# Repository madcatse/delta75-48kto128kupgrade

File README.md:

# 128k RAM expansion for ZX48k
Upgrade ZX Spectrum 48k with 128k of RAM and play all the games that you couldn't play before. The sound will stay as before, but you can buy an extension module (based on AY-3-8912 or AY-3-8910) to make it sound as ZX Spectrum 128k.

In order to make the RAM expansion work, a small modification to your ZX Spectrum 48k is required to disable 32k upper RAM.

For Issue 2-3-4, on IC23 cut and bend pin 1 and connect it to pin 14 (+5V). For Issue 5-6 cut pin 34 (CASL) on ZX8401 and connect it's via (not the pin) to pin 40 (+5V).

Попробовать восьмой пин U39 поднять и посадить туда +5В

https://spectrumcomputing.co.uk/forums/viewtopic.php?t=2616

With this mod without the RAM expansion, your ZX Spectrum 48k will work as ZX Spectrum 16k. 

Original page: https://velesoft.speccy.cz/zx/external_128kb_upgrade/index.htm

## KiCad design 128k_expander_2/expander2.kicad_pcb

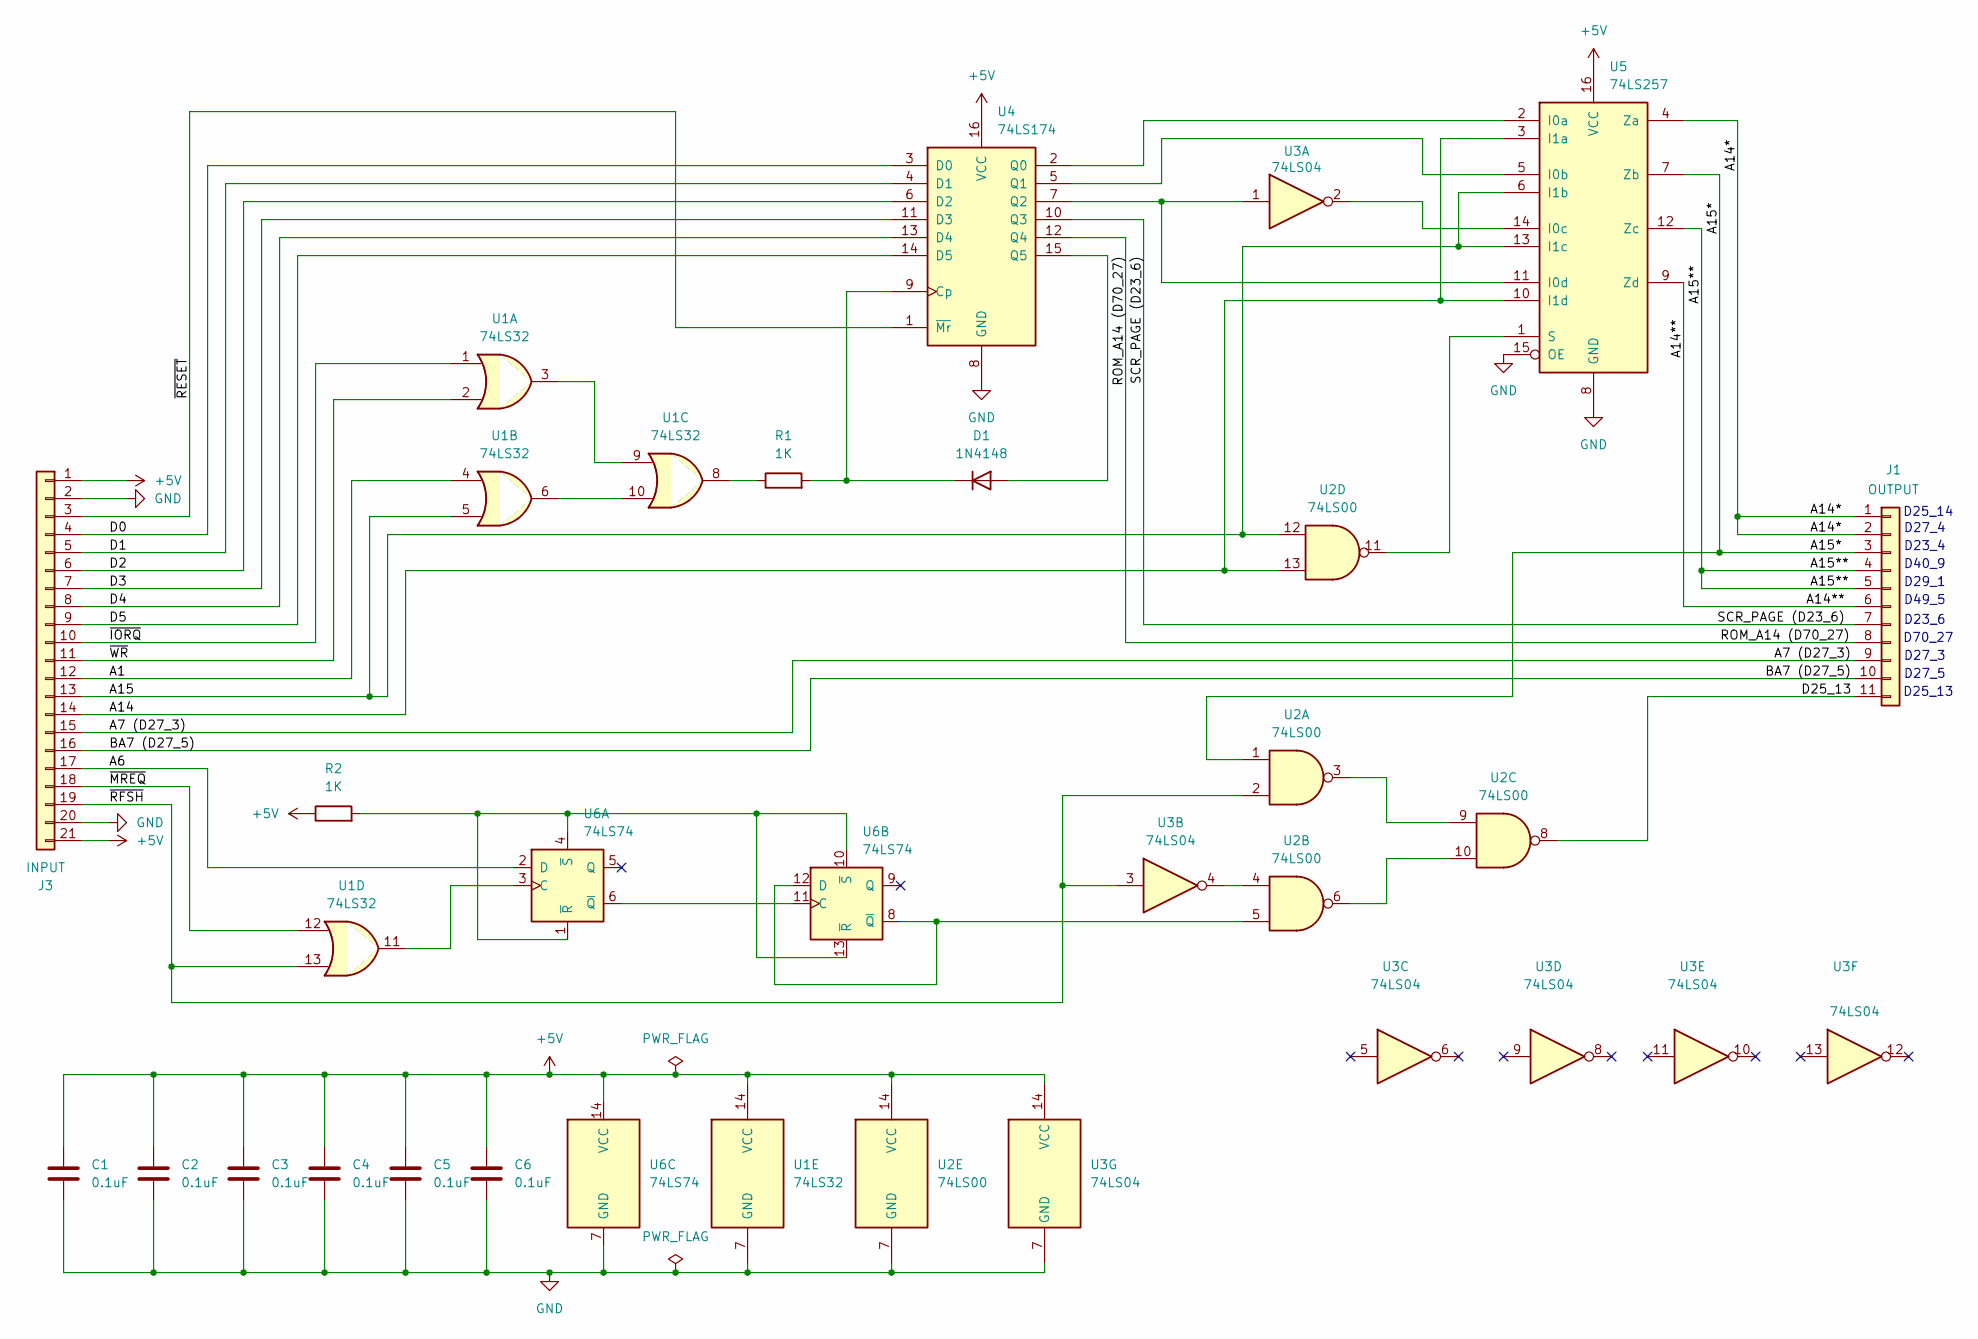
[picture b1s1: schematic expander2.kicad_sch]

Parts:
C1, C2, C3, C4, C5, C6: 0.1uF; C_Disc_D7.5mm_W2.5mm_P5.00mm
D1: 1N4148; D_DO-35_SOD27_P10.16mm_Horizontal
J1: OUTPUT; PinHeader_1x11_P2.54mm_Vertical
J3: INPUT; PinHeader_1x21_P2.54mm_Vertical
R1, R2: 1K; R_Axial_DIN0207_L6.3mm_D2.5mm_P10.16mm_Horizontal
U1: 74LS32; DIP-14_W7.62mm_Socket_LongPads
U2: 74LS00; DIP-14_W7.62mm_Socket_LongPads
U3: 74LS04; DIP-14_W7.62mm_Socket_LongPads
U4: 74LS174; DIP-16_W7.62mm_Socket_LongPads
U5: 74LS257; DIP-16_W7.62mm_Socket_LongPads
U6: 74LS74; DIP-14_W7.62mm_Socket_LongPads

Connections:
+5V: C1.1, C2.1, C3.1, C4.1, C5.1, C6.1, J3.1, J3.21, R2.1, U1.14 (VCC), U2.14 (VCC), U3.14 (VCC), U4.16 (VCC), U5.16 (VCC), U6.14 (VCC)
/A1: J3.12, U1.4
/A6: J3.17, U6.2 (D)
/A7 (D27_3): J1.9, J3.15
/A14: J3.14, U2.13, U5.3 (I1a), U5.10 (I1d)
/A14*: J1.1, J1.2, U5.4 (Za)
/A14**: J1.6, U5.9 (Zd)
/A15: J3.13, U1.5, U2.12, U5.6 (I1b), U5.13 (I1c)
/A15*: J1.3, U2.1, U5.7 (Zb)
/A15**: J1.4, J1.5, U5.12 (Zc)
/BA7 (D27_5): J1.10, J3.16
/D0: J3.4, U4.3 (D0)
/D1: J3.5, U4.4 (D1)
/D2: J3.6, U4.6 (D2)
/D3: J3.7, U4.11 (D3)
/D4: J3.8, U4.13 (D4)
/D5: J3.9, U4.14 (D5)
/D25_13: J1.11, U2.8
/ROM_A14 (D70_27): J1.8, U4.12 (Q4)
/SCR_PAGE (D23_6): J1.7, U4.10 (Q3)
/~IORQ: J3.10, U1.1
/~MREQ: J3.18, U1.12
/~RESET: J3.3, U4.1 (~Mr)
/~RFSH: J3.19, U1.13, U2.2, U3.3
/~WR: J3.11, U1.2
GND: C1.2, C2.2, C3.2, C4.2, C5.2, C6.2, J3.2, J3.20, U1.7 (GND), U2.7 (GND), U3.7 (GND), U4.8 (GND), U5.8 (GND), U5.15 (OE), U6.7 (GND)
unnamed: D1.2 (A), U4.15 (Q5)
unnamed: D1.1 (K), R1.2, U4.9 (Cp)
unnamed: R1.1, U1.8
unnamed: U1.3, U1.9
unnamed: U1.6, U1.10
unnamed: U2.3, U2.9
unnamed: U2.4, U3.4
unnamed: U2.6, U2.10
unnamed: U4.2 (Q0), U5.2 (I0a)
unnamed: U4.5 (Q1), U5.5 (I0b)
unnamed: U3.1, U4.7 (Q2), U5.11 (I0d)
unnamed: U3.2, U5.14 (I0c)
unnamed: U2.11, U5.1 (S)
unnamed: U1.11, U6.3 (C)
unnamed: U6.6 (~Q), U6.11 (C)
unnamed: R2.2, U6.1 (~R), U6.4 (~S), U6.10 (~S), U6.13 (~R)
unnamed: U2.5, U6.8 (~Q), U6.12 (D)

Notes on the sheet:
D70_27
D25_14
D40_9
D27_3
D29_1
D27_4
D49_5
D23_4
D25_13
D23_6
D27_5

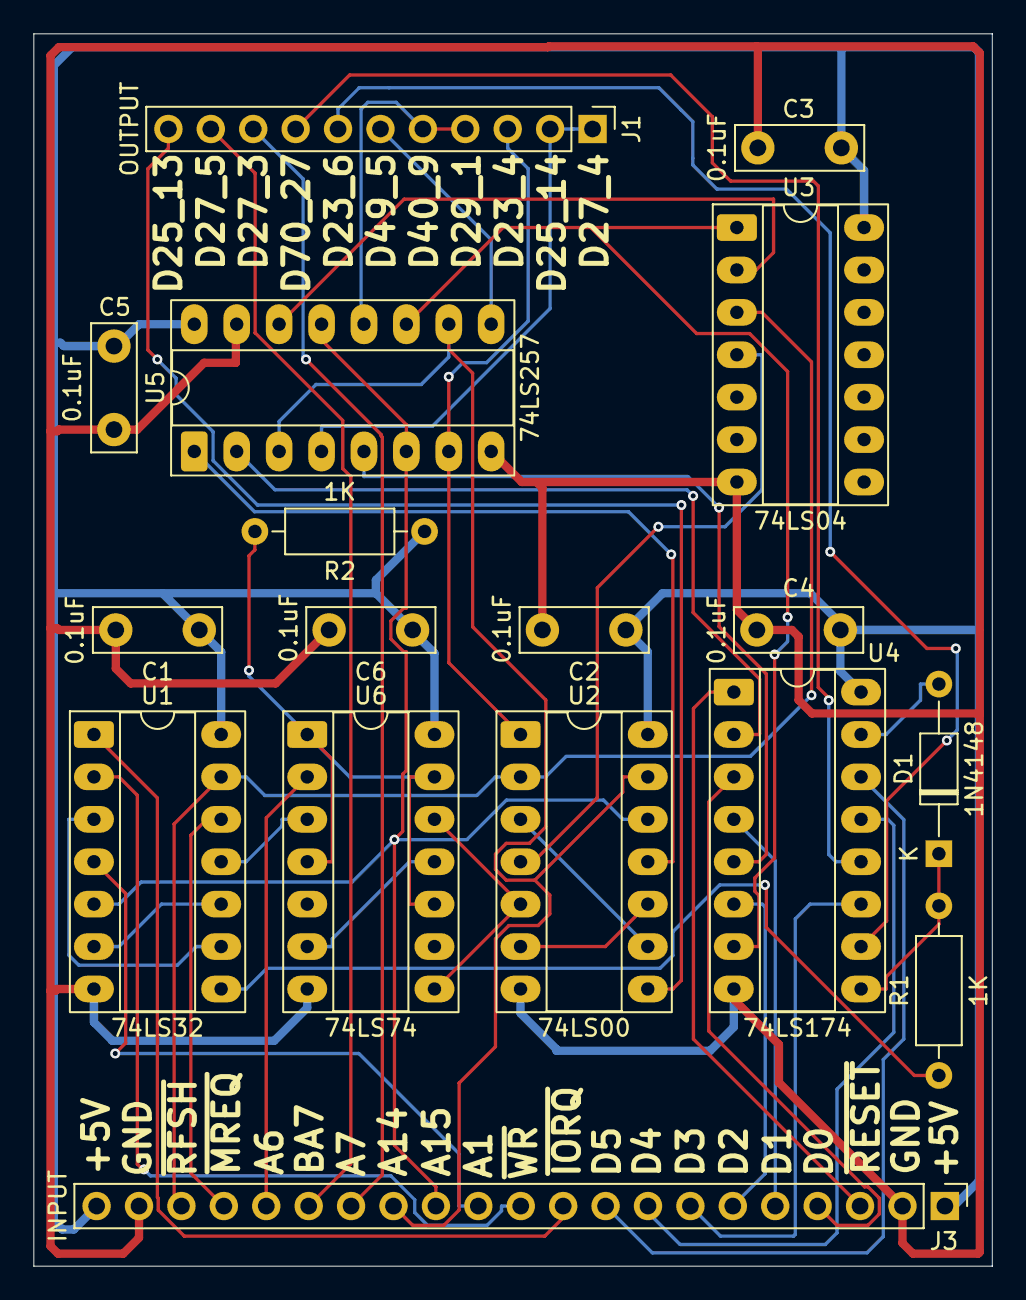
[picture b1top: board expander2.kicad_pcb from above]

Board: 2 copper layers, 57.4 x 73.8 mm, 17 parts (0 on the bottom side), 43 nets.

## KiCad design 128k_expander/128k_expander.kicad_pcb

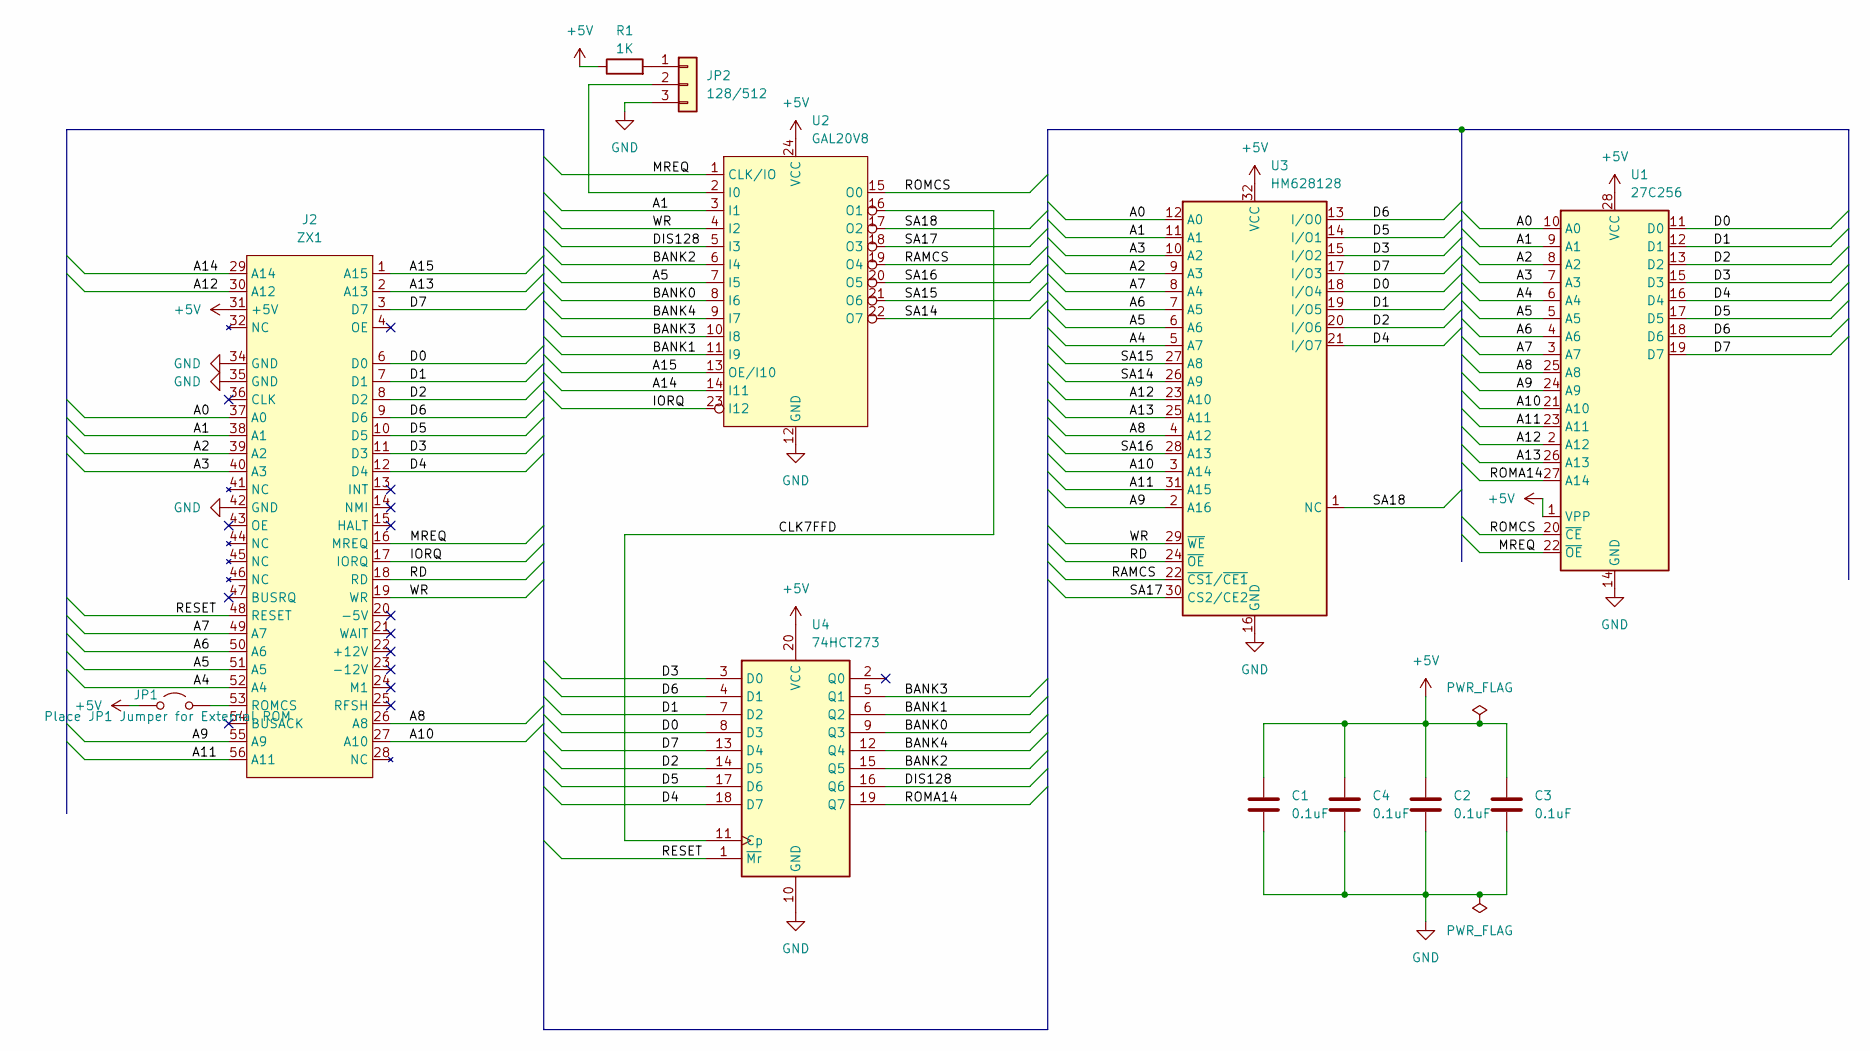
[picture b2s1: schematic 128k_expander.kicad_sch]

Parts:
C1, C2, C3, C4: 0.1uF; C_Disc_D7.5mm_W2.5mm_P5.00mm
J2: ZX1; ZX SPECTRUM EDGE CONNECTOR (HORIZONTAL)
JP1: Place JP1 Jumper for External ROM; PinHeader_1x02_P2.54mm_Vertical
JP2: 128/512; PinHeader_1x03_P2.54mm_Vertical
R1: 1K; R_Axial_DIN0207_L6.3mm_D2.5mm_P10.16mm_Horizontal
U1: 27C256; DIP-28_W15.24mm_LongPads
U2: GAL20V8; DIP-24_W7.62mm_LongPads
U3: HM628128; DIP-32_W15.24mm_LongPads
U4: 74HCT273; DIP-20_W7.62mm_LongPads

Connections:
+5V: C1.1, C2.1, C3.1, C4.1, J2.31 (+5V), JP1.1 (A), R1.1, U1.1 (VPP), U1.28 (VCC), U2.24 (VCC), U3.32 (VCC), U4.20 (VCC)
/A0: J2.37 (A0), U1.10 (A0), U3.12 (A0)
/A1: J2.38 (A1), U1.9 (A1), U2.3 (I1), U3.11 (A1)
/A2: J2.39 (A2), U1.8 (A2), U3.9 (A3)
/A3: J2.40 (A3), U1.7 (A3), U3.10 (A2)
/A4: J2.52 (A4), U1.6 (A4), U3.5 (A7)
/A5: J2.51 (A5), U1.5 (A5), U2.7 (I5), U3.6 (A6)
/A6: J2.50 (A6), U1.4 (A6), U3.7 (A5)
/A7: J2.49 (A7), U1.3 (A7), U3.8 (A4)
/A8: J2.26 (A8), U1.25 (A8), U3.4 (A12)
/A9: J2.55 (A9), U1.24 (A9), U3.2 (A16)
/A10: J2.27 (A10), U1.21 (A10), U3.3 (A14)
/A11: J2.56 (A11), U1.23 (A11), U3.31 (A15)
/A12: J2.30 (A12), U1.2 (A12), U3.23 (A10)
/A13: J2.2 (A13), U1.26 (A13), U3.25 (A11)
/A14: J2.29 (A14), U2.14 (I11)
/A15: J2.1 (A15), U2.13 (OE/I10)
/BANK0: U2.8 (I6), U4.9 (Q3)
/BANK1: U2.11 (I9), U4.6 (Q2)
/BANK2: U2.6 (I4), U4.15 (Q5)
/BANK3: U2.10 (I8), U4.5 (Q1)
/BANK4: U2.9 (I7), U4.12 (Q4)
/CLK7FFD: U2.16 (O1), U4.11 (Cp)
/D0: J2.6 (D0), U1.11 (D0), U3.18 (I/O4), U4.8 (D3)
/D1: J2.7 (D1), U1.12 (D1), U3.19 (I/O5), U4.7 (D2)
/D2: J2.8 (D2), U1.13 (D2), U3.20 (I/O6), U4.14 (D5)
/D3: J2.11 (D3), U1.15 (D3), U3.15 (I/O2), U4.3 (D0)
/D4: J2.12 (D4), U1.16 (D4), U3.21 (I/O7), U4.18 (D7)
/D5: J2.10 (D5), U1.17 (D5), U3.14 (I/O1), U4.17 (D6)
/D6: J2.9 (D6), U1.18 (D6), U3.13 (I/O0), U4.4 (D1)
/D7: J2.3 (D7), U1.19 (D7), U3.17 (I/O3), U4.13 (D4)
/DIS128: U2.5 (I3), U4.16 (Q6)
/IORQ: J2.17 (IORQ), U2.23 (I12)
/MREQ: J2.16 (MREQ), U1.22 (~OE), U2.1 (CLK/IO)
/RAMCS: U2.19 (O4), U3.22 (~CS1/~CE1)
/RD: J2.18 (RD), U3.24 (~OE)
/RESET: J2.48 (RESET), U4.1 (~Mr)
/ROMA14: U1.27 (A14), U4.19 (Q7)
/ROMCS: U1.20 (~CE), U2.15 (O0)
/SA14: U2.22 (O7), U3.26 (A9)
/SA15: U2.21 (O6), U3.27 (A8)
/SA16: U2.20 (O5), U3.28 (A13)
/SA17: U2.18 (O3), U3.30 (CS2/CE2)
/SA18: U2.17 (O2), U3.1 (NC)
/WR: J2.19 (WR), U2.4 (I2), U3.29 (~WE)
GND: C1.2, C2.2, C3.2, C4.2, J2.34 (GND), J2.35 (GND), J2.42 (GND), JP2.3, U1.14 (GND), U2.12 (GND), U3.16 (GND), U4.10 (GND)
unnamed: J2.53 (ROMCS), JP1.2 (B)
unnamed: JP2.1, R1.2
unnamed: JP2.2, U2.2 (I0)

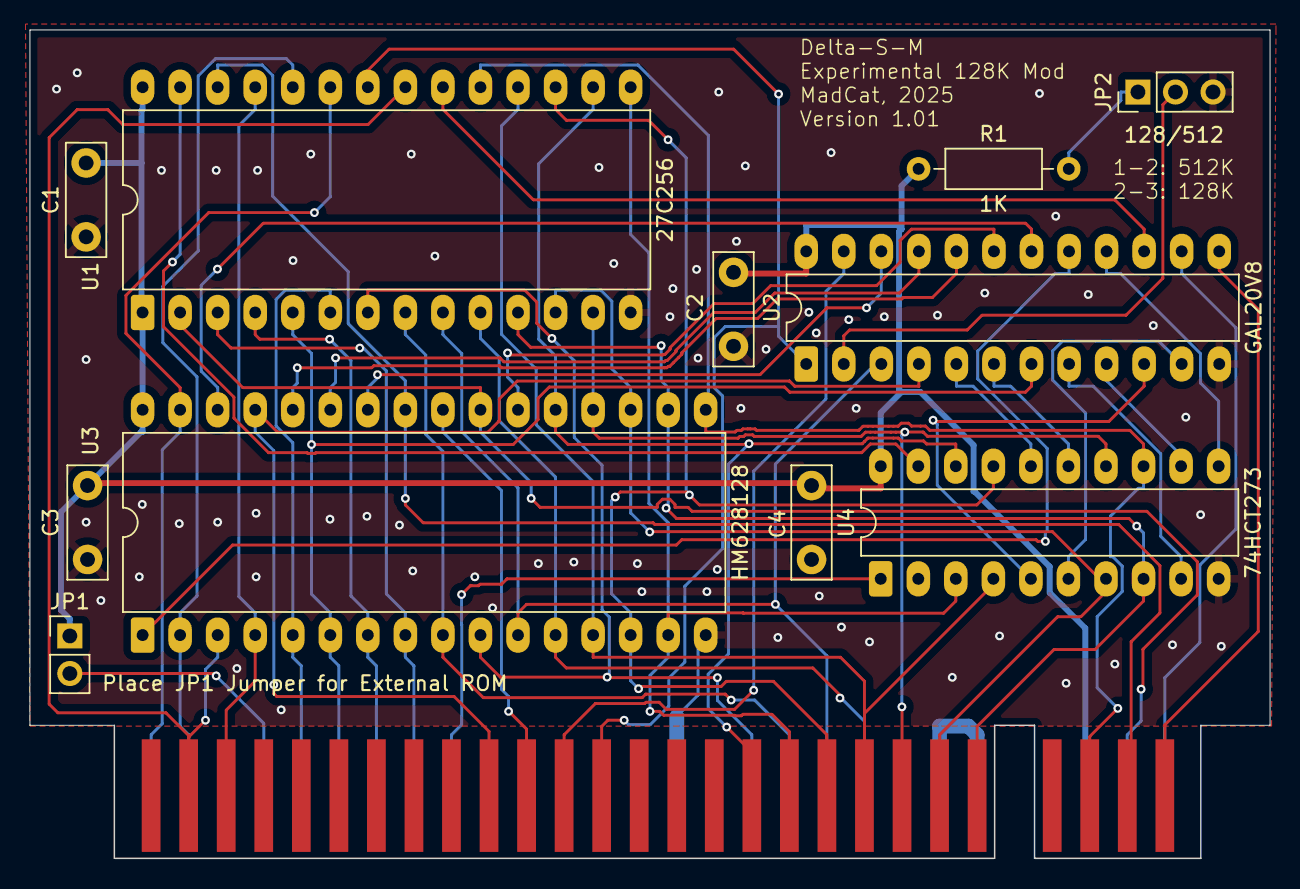
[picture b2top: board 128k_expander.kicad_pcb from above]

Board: 2 copper layers, 83.9 x 56.0 mm, 12 parts (0 on the bottom side), 49 nets.

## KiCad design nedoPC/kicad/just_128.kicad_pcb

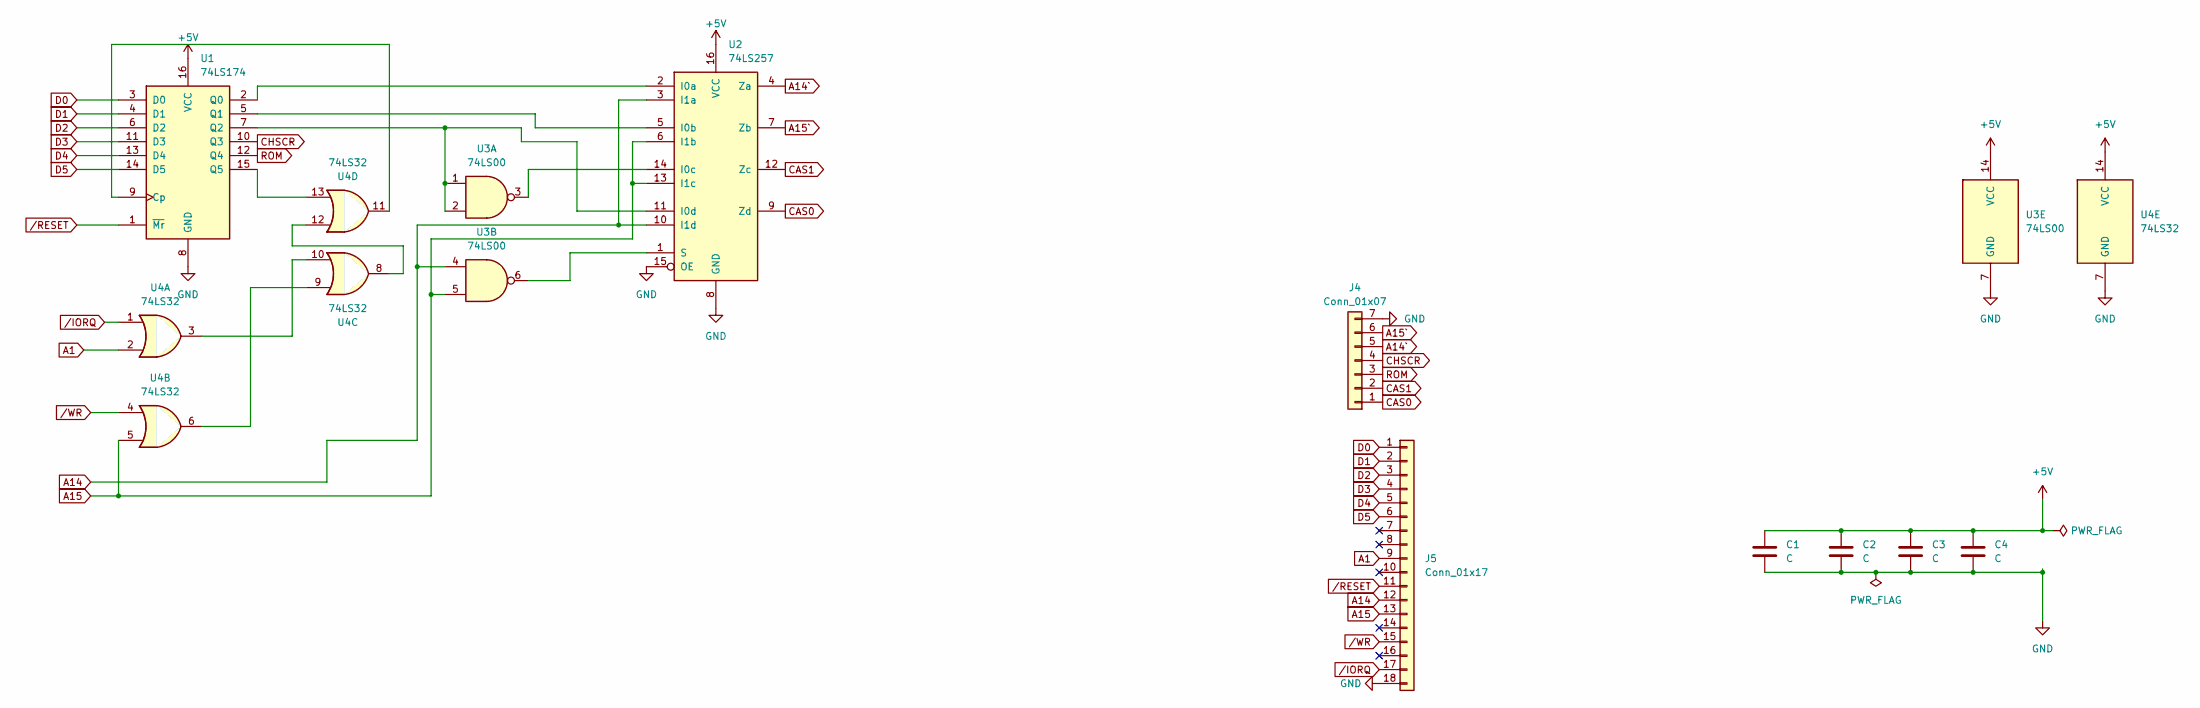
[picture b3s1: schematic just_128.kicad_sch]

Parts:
C1, C2, C3, C4: C; C_Disc_D7.0mm_W2.5mm_P5.00mm
J4: Conn_01x07; PinSocket_1x07_P2.54mm_Horizontal
J5: Conn_01x17; PinSocket_1x18_P2.54mm_Horizontal
U1: 74LS174; DIP-16_W7.62mm_Socket
U2: 74LS257; DIP-16_W7.62mm_Socket
U3: 74LS00; DIP-14_W7.62mm_Socket
U4: 74LS32; DIP-14_W7.62mm_Socket

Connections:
+5V: C1.1, C2.1, C3.1, C4.1, U1.16 (VCC), U2.16 (VCC), U3.14 (VCC), U4.14 (VCC)
A1: J5.9, U4.2
A14: J5.12, U2.3 (I1a), U2.10 (I1d), U3.4
A14`: J4.5, U2.4 (Za)
A15: J5.13, U2.6 (I1b), U2.13 (I1c), U3.5, U4.5
A15`: J4.6, U2.7 (Zb)
CAS0: J4.1, U2.9 (Zd)
CAS1: J4.2, U2.12 (Zc)
CHSCR: J4.4, U1.10 (Q3)
D0: J5.1, U1.3 (D0)
D1: J5.2, U1.4 (D1)
D2: J5.3, U1.6 (D2)
D3: J5.4, U1.11 (D3)
D4: J5.5, U1.13 (D4)
D5: J5.6, U1.14 (D5)
GND: C1.2, C2.2, C3.2, C4.2, J4.7, J5.18, U1.8 (GND), U2.8 (GND), U2.15 (OE), U3.7 (GND), U4.7 (GND)
unnamed: U1.9 (Cp), U4.11
unnamed: U1.2 (Q0), U2.2 (I0a)
unnamed: U1.5 (Q1), U2.5 (I0b)
unnamed: U1.7 (Q2), U2.11 (I0d), U3.1, U3.2
unnamed: U1.15 (Q5), U4.13
unnamed: U2.14 (I0c), U3.3
unnamed: U2.1 (S), U3.6
unnamed: U4.6, U4.9
unnamed: U4.3, U4.10
unnamed: U4.8, U4.12
ROM: J4.3, U1.12 (Q4)
/IORQ: J5.17, U4.1
/RESET: J5.11, U1.1 (~Mr)
/WR: J5.15, U4.4

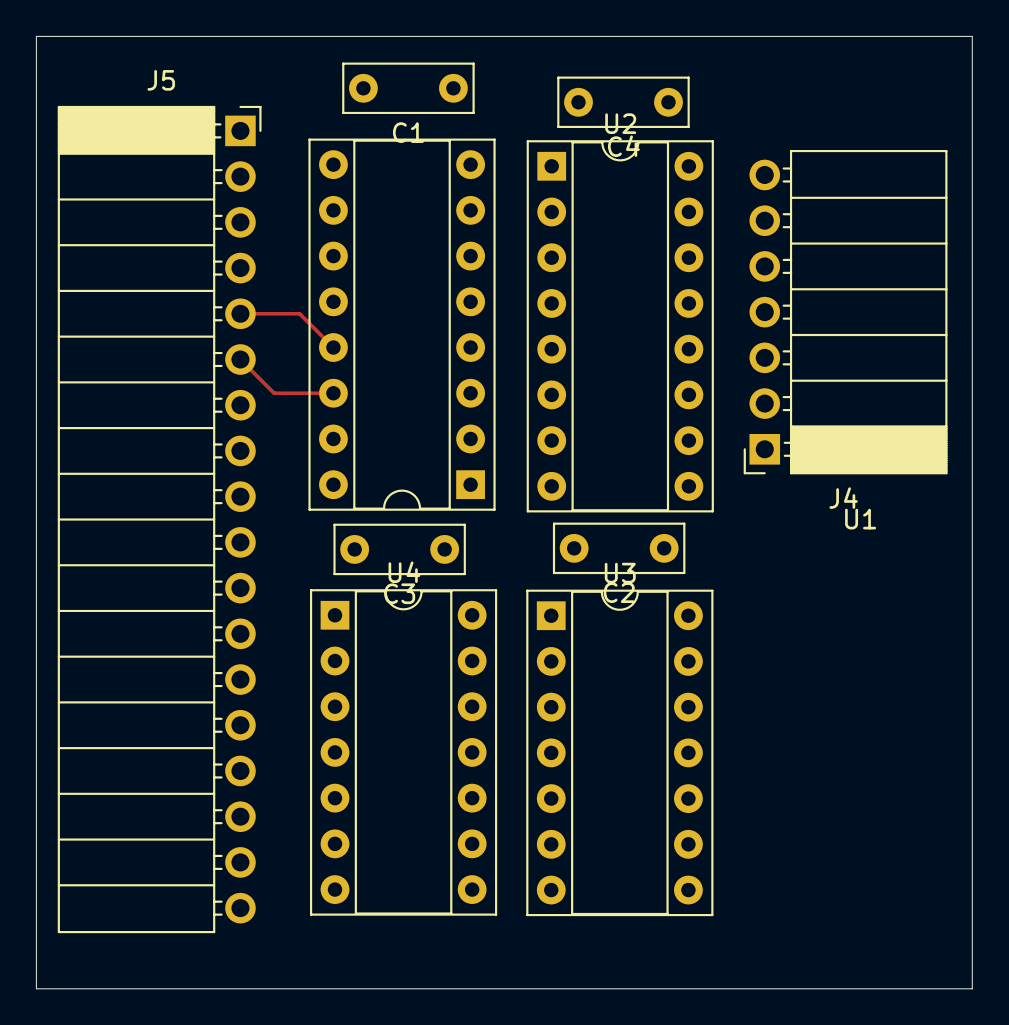
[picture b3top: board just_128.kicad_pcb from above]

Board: 2 copper layers, 52.0 x 52.9 mm, 10 parts (0 on the bottom side), 30 nets.

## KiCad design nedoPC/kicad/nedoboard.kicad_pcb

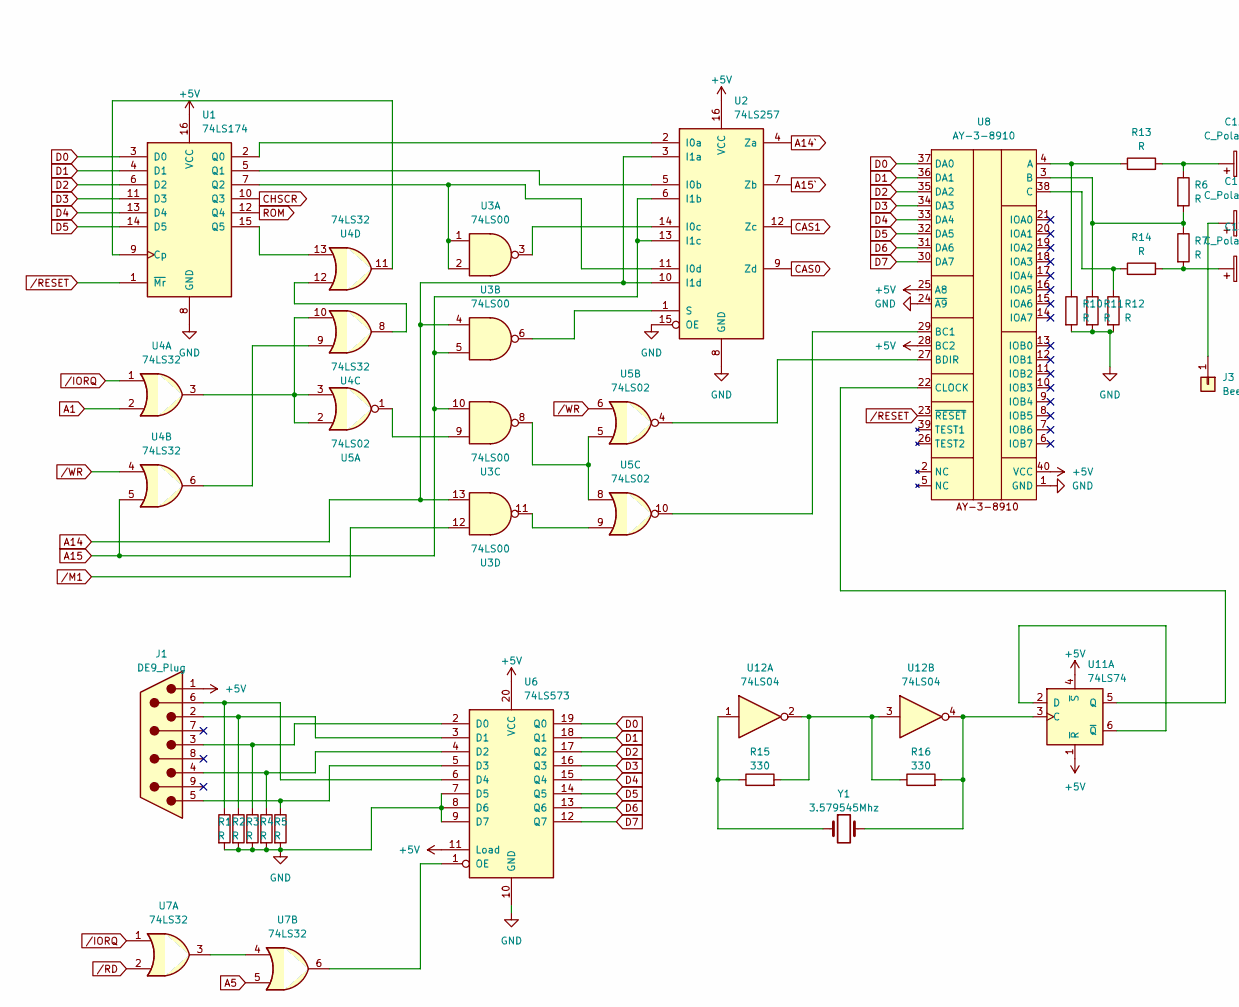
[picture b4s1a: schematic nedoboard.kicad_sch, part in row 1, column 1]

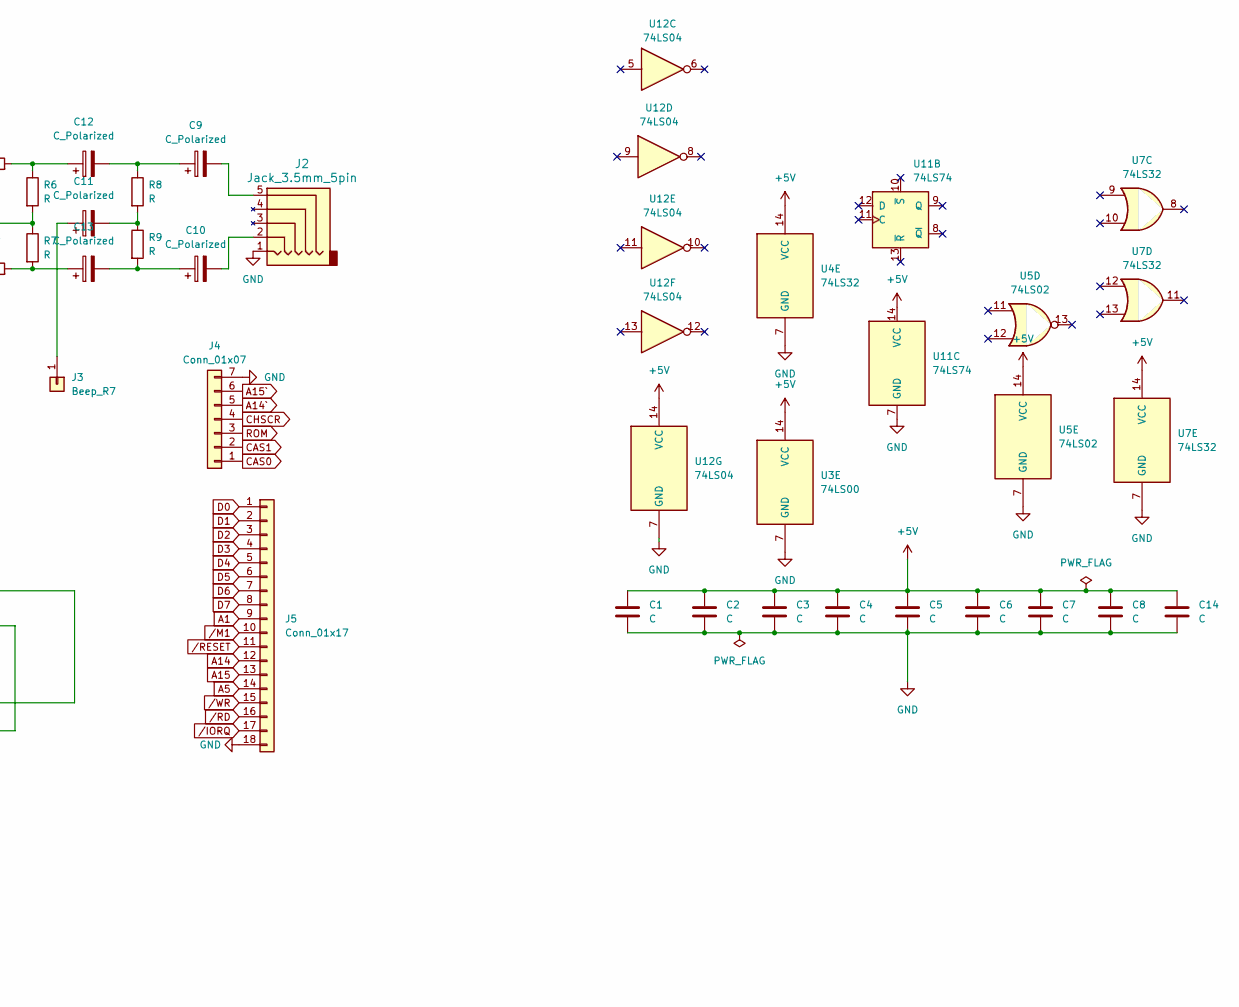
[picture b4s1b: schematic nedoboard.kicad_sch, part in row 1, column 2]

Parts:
C1, C2, C3, C4, C5, C6, C7, C8, C14: C; C_Disc_D7.0mm_W2.5mm_P5.00mm
C9, C10, C11, C12, C13: C_Polarized; CP_Radial_D8.0mm_P3.80mm
J1: DE9_Plug; DSUB-9_Male_Horizontal_P2.77x2.84mm_EdgePinOffset4.94mm_Hou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
J2: Jack_3.5mm_5pin; jack_5_pin_3f07_FINAL
J3: Beep_R7; SolderWire-0.75sqmm_1x01_D1.25mm_OD3.5mm
J4: Conn_01x07; PinSocket_1x07_P2.54mm_Horizontal
J5: Conn_01x17; PinSocket_1x18_P2.54mm_Horizontal
R1, R2, R3, R4, R5, R6, R7, R8, R9, R10, R11, R12, R13, R14: R; R_Axial_DIN0207_L6.3mm_D2.5mm_P7.62mm_Horizontal
R15, R16: 330; R_Axial_DIN0207_L6.3mm_D2.5mm_P7.62mm_Horizontal
U1: 74LS174; DIP-16_W7.62mm_Socket
U2: 74LS257; DIP-16_W7.62mm_Socket
U3: 74LS00; DIP-14_W7.62mm_Socket
U4, U7: 74LS32; DIP-14_W7.62mm_Socket
U5: 74LS02; DIP-14_W7.62mm_Socket
U6: 74LS573; DIP-20_W7.62mm_Socket
U8: AY-3-8910; DIP-40_W15.24mm_Socket
U11: 74LS74; DIP-14_W7.62mm_Socket
U12: 74LS04; DIP-14_W7.62mm_Socket
Y1: 3.579545Mhz; Crystal_HC49-U_Horizontal

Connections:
+5V: C1.1, C2.1, C3.1, C4.1, C5.1, C6.1, C7.1, C8.1, C14.1, J1.1, U1.16 (VCC), U2.16 (VCC), U3.14 (VCC), U4.14 (VCC), U5.14 (VCC), U6.11 (Load), U6.20 (VCC), U7.14 (VCC), U8.25 (A8), U8.28 (BC2), U8.40 (VCC), U11.1 (~R), U11.4 (~S), U11.14 (VCC), U12.14 (VCC)
A1: J5.9, U4.2
A5: J5.14, U7.5
A14: J5.12, U2.3 (I1a), U2.10 (I1d), U3.4, U3.13
A14`: J4.5, U2.4 (Za)
A15: J5.13, U2.6 (I1b), U2.13 (I1c), U3.5, U3.10, U4.5
A15`: J4.6, U2.7 (Zb)
CAS0: J4.1, U2.9 (Zd)
CAS1: J4.2, U2.12 (Zc)
CHSCR: J4.4, U1.10 (Q3)
D0: J5.1, U1.3 (D0), U6.19 (Q0), U8.37 (DA0)
D1: J5.2, U1.4 (D1), U6.18 (Q1), U8.36 (DA1)
D2: J5.3, U1.6 (D2), U6.17 (Q2), U8.35 (DA2)
D3: J5.4, U1.11 (D3), U6.16 (Q3), U8.34 (DA3)
D4: J5.5, U1.13 (D4), U6.15 (Q4), U8.33 (DA4)
D5: J5.6, U1.14 (D5), U6.14 (Q5), U8.32 (DA5)
D6: J5.7, U6.13 (Q6), U8.31 (DA6)
D7: J5.8, U6.12 (Q7), U8.30 (DA7)
GND: C1.2, C2.2, C3.2, C4.2, C5.2, C6.2, C7.2, C8.2, C14.2, J2.1, J4.7, J5.18, R1.2, R2.2, R3.2, R4.2, R5.2, R10.2, R11.2, R12.2, U1.8 (GND), U2.8 (GND), U2.15 (OE), U3.7 (GND), U4.7 (GND), U5.7 (GND), U6.7 (D5), U6.8 (D6), U6.9 (D7), U6.10 (GND), U7.7 (GND), U8.1 (GND), U8.24 (~A9), U11.7 (GND), U12.7 (GND)
unnamed: C9.2, J2.5
unnamed: C10.1, C13.2, R9.2
unnamed: C10.2, J2.2
unnamed: C11.2, R8.2, R9.1
unnamed: C12.1, R6.1, R13.2
unnamed: C9.1, C12.2, R8.1
unnamed: C13.1, R7.2, R14.2
unnamed: C11.1, J3.1
unnamed: R15.1, U12.1, Y1.1
unnamed: R15.2, R16.1, U12.2, U12.3
unnamed: U1.9 (Cp), U4.11
unnamed: U1.2 (Q0), U2.2 (I0a)
unnamed: U1.5 (Q1), U2.5 (I0b)
unnamed: U1.7 (Q2), U2.11 (I0d), U3.1, U3.2
unnamed: U1.15 (Q5), U4.13
unnamed: U2.14 (I0c), U3.3
unnamed: U2.1 (S), U3.6
unnamed: U3.8, U5.5, U5.8
unnamed: U3.9, U5.1
unnamed: U3.11, U5.9
unnamed: U4.6, U4.9
unnamed: U4.3, U4.10, U5.2, U5.3
unnamed: U4.8, U4.12
unnamed: J1.3, R3.1, U6.2 (D0)
unnamed: J1.2, R2.1, U6.3 (D1)
unnamed: J1.4, R4.1, U6.4 (D2)
unnamed: J1.5, R5.1, U6.5 (D3)
unnamed: J1.6, R1.1, U6.6 (D4)
unnamed: U6.1 (OE), U7.6
unnamed: U7.3, U7.4
unnamed: R10.1, R13.1, U8.4 (A)
unnamed: R6.2, R7.1, R11.1, U8.3 (B)
unnamed: U5.10, U8.29 (BC1)
unnamed: U5.4, U8.27 (BDIR)
unnamed: R12.1, R14.1, U8.38 (C)
unnamed: R16.2, U11.3 (C), U12.4, Y1.2
unnamed: U11.2 (D), U11.6 (~Q)
unnamed: U8.22 (CLOCK), U11.5 (Q)
ROM: J4.3, U1.12 (Q4)
/IORQ: J5.17, U4.1, U7.1
/M1: J5.10, U3.12
/RD: J5.16, U7.2
/RESET: J5.11, U1.1 (~Mr), U8.23 (~RESET)
/WR: J5.15, U4.4, U5.6

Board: 2 copper layers, 46 parts (0 on the bottom side), 63 nets, no tracks yet.

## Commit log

2023-09-17 Begin_work
2024-05-31 New board
2024-12-14 Small update
2024-12-20 NedoPC import
2024-12-20 Update nedopc
2025-03-24 128 Expander
